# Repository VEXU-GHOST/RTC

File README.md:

# RTC
Repo for RTC board for the Jetson Orin Nano

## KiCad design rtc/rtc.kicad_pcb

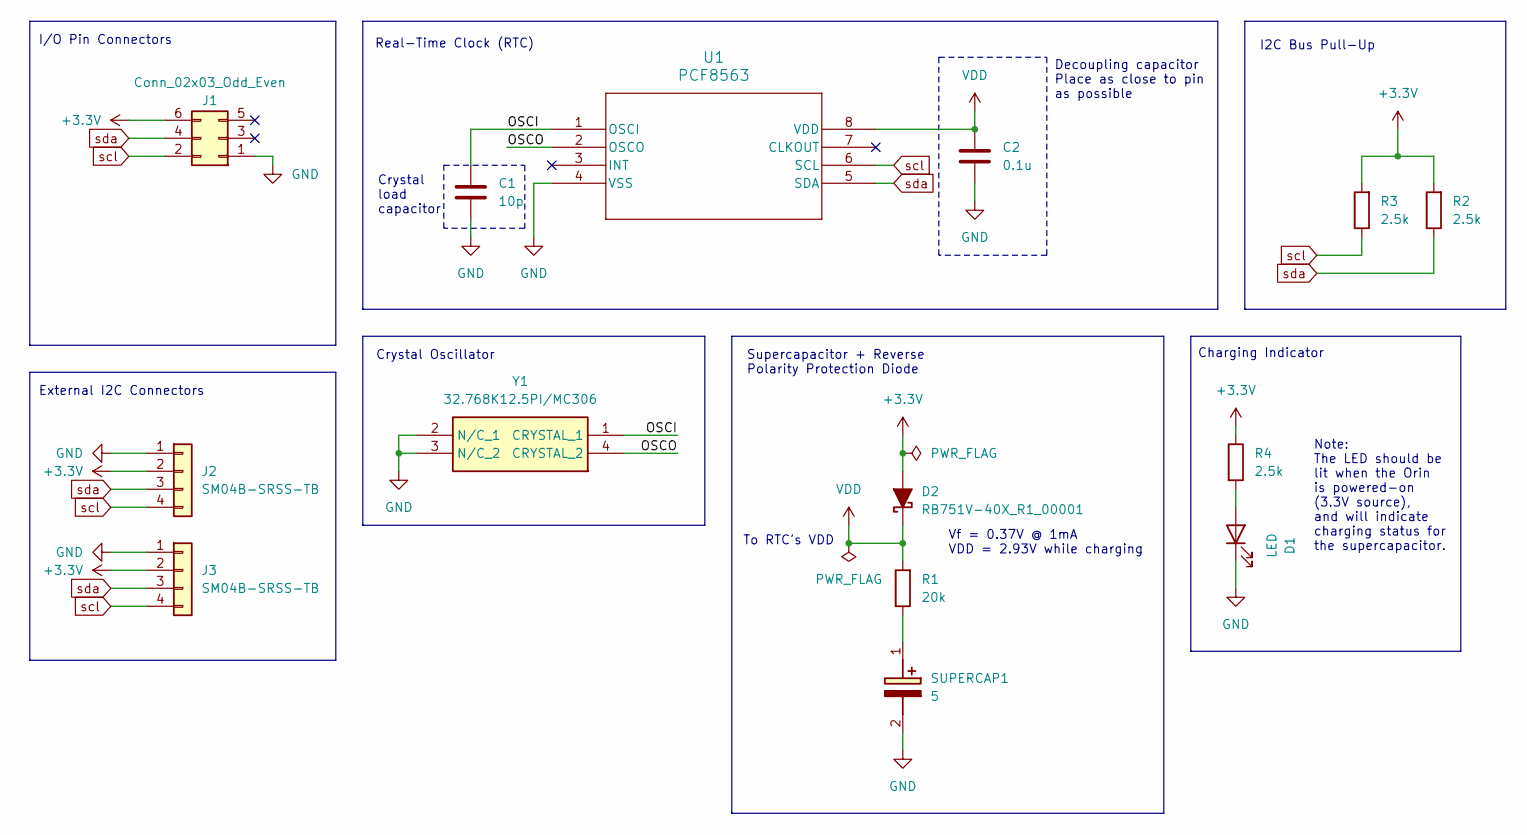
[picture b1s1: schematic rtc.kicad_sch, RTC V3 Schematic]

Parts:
C1: 10p; C_0603_1608Metric_Pad1.08x0.95mm_HandSolder; Manufacturer Part Number CGA0603C0G100J500JT
C2: 0.1u; C_0603_1608Metric_Pad1.08x0.95mm_HandSolder; Manufacturer Part Number CGA0603X7R104K500JT
D1: LED; LED_0603_1608Metric_Pad1.05x0.95mm_HandSolder; Manufacturer Part Number XL-1608SURC-06
D2: RB751V-40X_R1_00001; SODFL2512X90N; Manufacturer Part Number RB751V-40X_R1_00001
J1: Conn_02x03_Odd_Even; PinSocket_2x03_P2.54mm_Vertical
J2, J3: SM04B-SRSS-TB; SM04BSRSSTB; Manufacturer Part Number XY-SM04B-SRSS-TB
R1: 20k; R_0603_1608Metric_Pad0.98x0.95mm_HandSolder; Manufacturer Part Number FRQ0603F2002TS
R2, R3, R4: 2.5k; R_0603_1608Metric_Pad0.98x0.95mm_HandSolder; Manufacturer Part Number FRC0603F2551TS
SUPERCAP1: 5; CE5R5505HFZJ; Manufacturer Part Number CE5R5505HF-ZJ
U1: PCF8563; PCF8563T_5_518_U_SO8_NXP; Manufacturer Part Number PCF8563T/5,518
Y1: 32.768K12.5PI/MC306; LFXTAL016178REEL; Mouser Part Number 449-LFXTAL016178REEL

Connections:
+3.3V: D2.2 (A), J1.6, J2.2, J3.2, R2.2, R3.2, R4.1
/OSCI: C1.1, U1.1 (OSCI), Y1.1 (CRYSTAL_1)
/OSCO: U1.2 (OSCO), Y1.4 (CRYSTAL_2)
GND: C1.2, C2.2, D1.1 (K), J1.1, J2.1, J3.1, SUPERCAP1.2 (-), U1.4 (VSS), Y1.2 (N/C_1), Y1.3 (N/C_2)
unnamed: D1.2 (A), R4.2
unnamed: R1.1, SUPERCAP1.1 (+)
VDD: C2.1, D2.1 (K), R1.2, U1.8 (VDD)
scl: J1.2, J2.4, J3.4, R3.1, U1.6 (SCL)
sda: J1.4, J2.3, J3.3, R2.1, U1.5 (SDA)

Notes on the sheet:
Supercapacitor + Reverse Polarity Protection Diode
I/O Pin Connectors
I2C Bus Pull-Up
Vf = 0.37V @ 1mA VDD = 2.93V while charging
Real-Time Clock (RTC)
To RTC's VDD
Crystal Oscillator
Note: The LED should be lit when the Orin is powered-on (3.3V source), and will indicate charging status for the supercapacitor.
Decoupling capacitor Place as close to pin as possible
Charging Indicator
External I2C Connectors
Crystal load capacitor

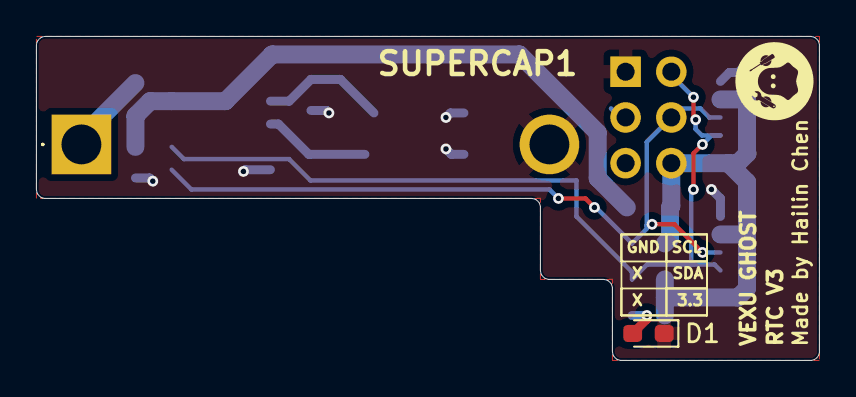
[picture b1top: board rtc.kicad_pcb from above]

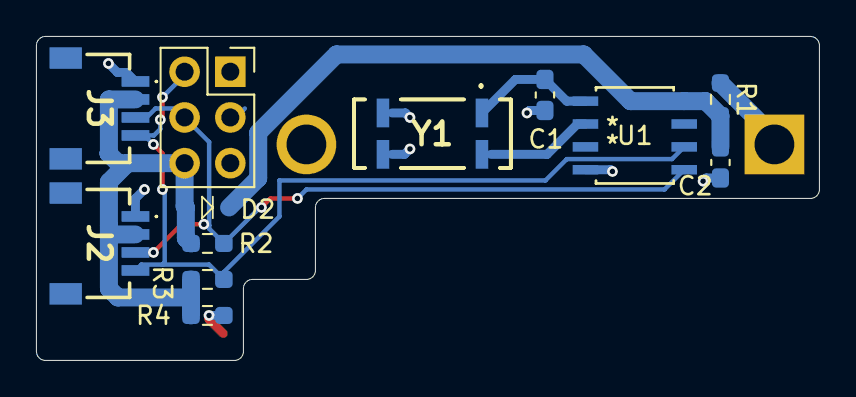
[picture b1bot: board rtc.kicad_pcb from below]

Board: 2 copper layers, 43.5 x 18.0 mm, 14 parts (12 on the bottom side), 9 nets.
